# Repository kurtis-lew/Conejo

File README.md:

# Conejo

## Overview

The Conejo is an OSH split, columnar-staggered, 54-key keyboard inspired by the [Iris](https://keeb.io/products/iris-keyboard-split-ergonomic-keyboard), [Lily58](https://github.com/kata0510/Lily58), and [Corne](https://github.com/foostan/crkbd) and powered by the [ZMK Firmware](https://github.com/zmkfirmware/zmk).

For more information, see the [project wiki](https://github.com/kurtis-lew/Conejo/wiki).

## Repository Structure
- KiCAD Project files are located in the root folder
- Gerbers for PCB fabrication are located in `exports/gerbers`.
- `.3mf` files for 3D printing cases are located in `exports/3D`
- An interactive BOM is located in `exports/bom`

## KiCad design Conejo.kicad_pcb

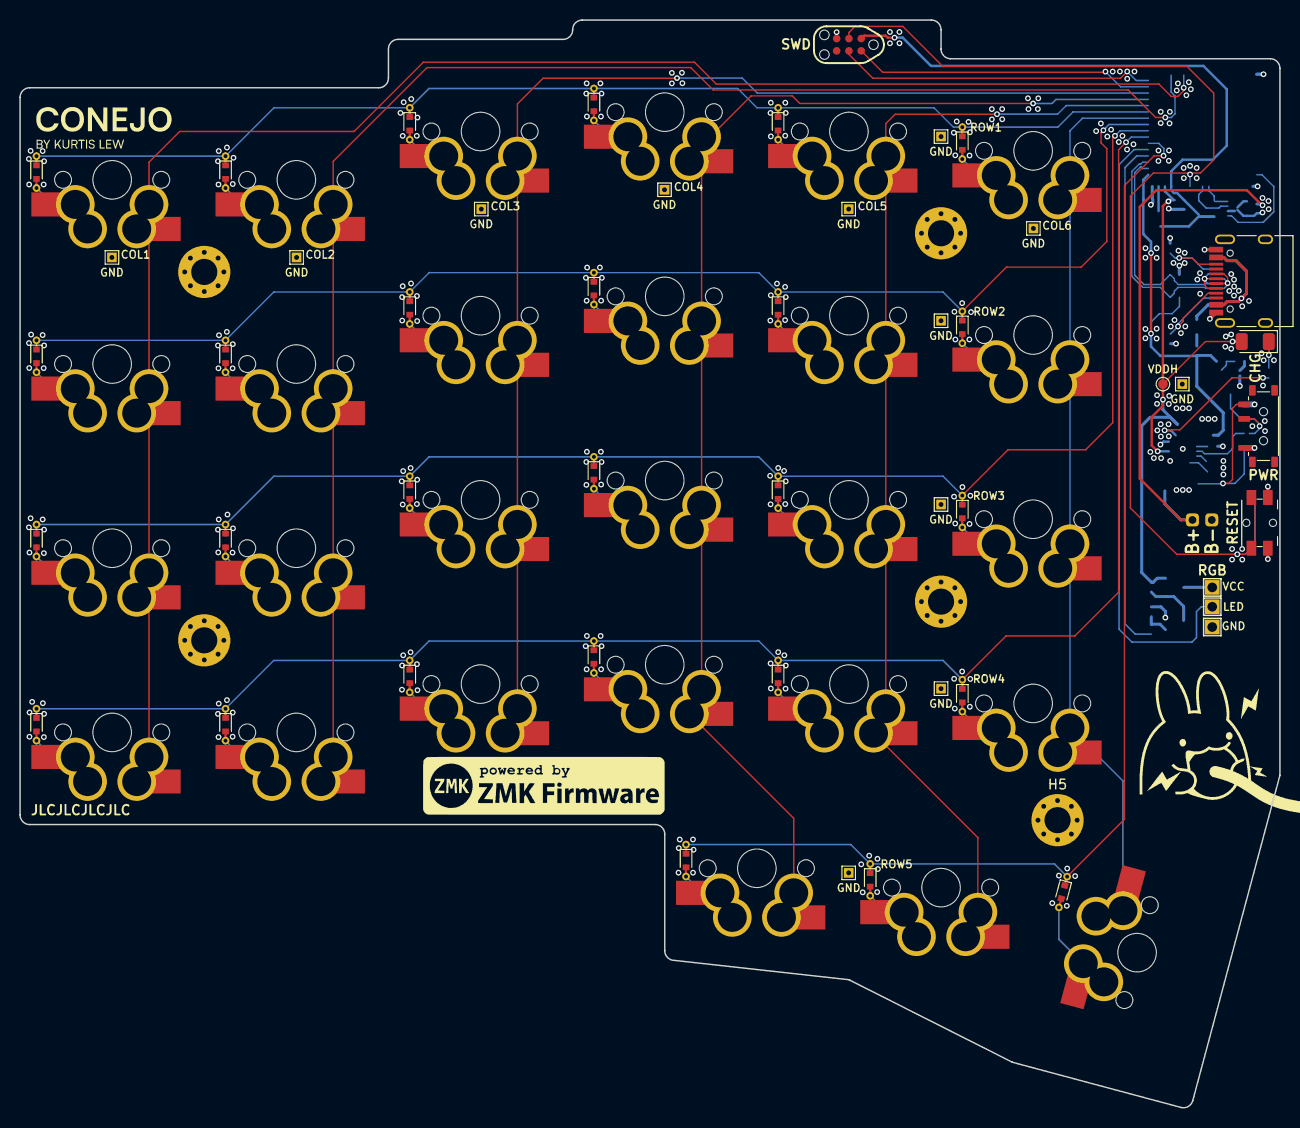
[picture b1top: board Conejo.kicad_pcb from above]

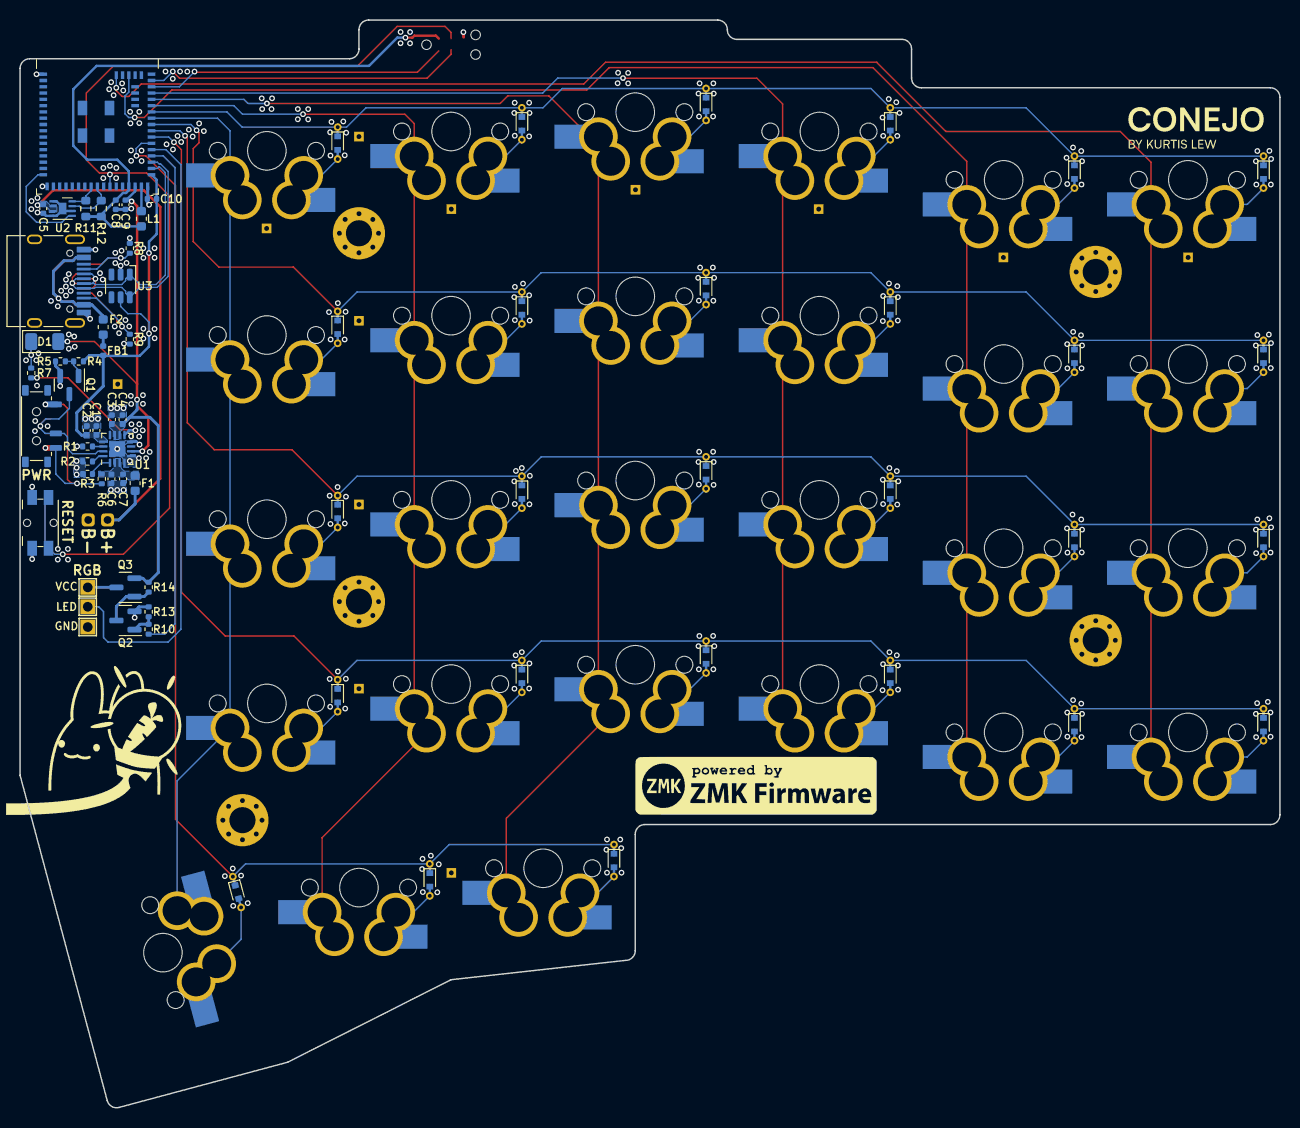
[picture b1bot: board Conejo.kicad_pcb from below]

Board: 4 copper layers, 130.3 x 112.5 mm, 116 parts (40 on the bottom side), 70 nets.

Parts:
C1, C2, C3, C4, C6, C7, C8, C9, C10: 4u7F; C_0402_1005Metric
C5: 100nF; C_0402_1005Metric
D1: CHG; LED_1206_3216Metric (Reversible)
D3, D4, D5, D6, D7, D8, D9, D10, D11, D12, D13, D14, D15, D16, D17, D18, D19, D20, D21, D22, D23, D24, D25, D26, D27, D28, D29: 1N4148; D_SOD-523 (Reversible)
F1, F2: 500mA; Fuse_0603_1608Metric
FB1: 120R@100MHz; L_0402_1005Metric
G1, G2: LOGO; Powered_By_ZMK (Large)
H1, H2, H3, H4, H5: M2.5; MountingHole_2.7mm_Pad_Via
J1: BATT; Battery Header
J2: HRO_TYPE-C-31-M-12; USB_C_Receptacle_HRO_TYPE-C-31-M-12 (Reversible)
J3: JTAG_TC2030; CON_TC2030_outlined
J4: RGB; LED Header
L1: 10uH; L_0603_1608Metric
Q1, Q2: 2N7002; SOT-23
Q3: AO3407; SOT-23
R1: RTMR; R_0402_1005Metric
R2: RSET; R_0402_1005Metric
R3, R5, R13, R14: 10K; R_0402_1005Metric
R4, R10: 100R; R_0402_1005Metric
R6: 100K; R_0402_1005Metric
R7: 1K5; R_0402_1005Metric
R8, R9: 5K1; R_0402_1005Metric
R11, R12: 5K1; R_0603_1608Metric
SW1: PWR; SW_MSK12C02-HB (Reversible)
SW2, SW3, SW4, SW5, SW6, SW7, SW8, SW9, SW10, SW11, SW12, SW13, SW14, SW15, SW16, SW17, SW18, SW19, SW20, SW21, SW22, SW23, SW24, SW25, SW26, SW27: MX Hotswap; MXOnly-1U-Hotswap (Reversible)
SW28: MX Hotswap; MXOnly-1.5U-Hotswap (Reversible)
SW29: RESET; Panasonic_EVQPUL_EVQPUC (Reversible)
TP1, TP1#2, TP1#3, TP1#4, TP1#5, TP1#6, TP1#7, TP1#8, TP1#9, TP1#10, TP1#11, TP1#12: GND; TestPoint_THTPad_1.0x1.0mm_Drill0.5mm
TP2: VDDH; TestPoint_Pad_D1.0mm
U1: BQ24075RGT; VQFN-16-1EP_3x3mm_P0.5mm_EP1.6x1.6mm
U2: MAX17048; TDFN-8-1EP_2x2mm_P0.5mm_EP0.8x1.2mm
U3: SRV05-4; SOT-23-6-routable
U4: MS88SF3; MS88SF3_V2

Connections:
+5V: C1.1, C2.2, C10.1, FB1.2, R4.1, U1.13 (IN), U3.5 (VP), U4.35 (VBUS)
+BATT: C5.1, F1.2, J1.1, U2.2 (CELL), U2.3 (VDD)
/Power Management/CHG: R7.1, U1.9 (~CHG)
/Power Management/ISET: R2.2, U1.16 (ISET)
/Power Management/SYSOFF: Q1.3 (D), SW1.2 (B), U1.15 (SYSOFF)
/Power Management/TMR: R1.2, U1.14 (TMR)
/Power Management/TS: R3.2, U1.1 (TS)
/USB-C/CC1: J2.A5 (CC1), R9.1
/USB-C/CC2: J2.B5 (CC2), R8.2
ALERT: U2.5 (ALERT), U4.17 (P0.26)
COL1: SW2.1, SW3.1, SW4.1, SW5.1, U4.56 (P0.10)
COL2: SW6.1, SW7.1, SW8.1, SW9.1, U4.54 (P1.06)
COL3: SW10.1, SW11.1, SW12.1, SW13.1, U4.48 (P0.25)
COL4: SW14.1, SW15.1, SW16.1, SW17.1, SW18.1, U4.47 (P1.00)
COL5: SW19.1, SW20.1, SW21.1, SW22.1, SW23.1, U4.46 (P0.24)
COL6: SW24.1, SW25.1, SW26.1, SW27.1, SW28.1, U4.44 (P0.20)
D+: J2.A6 (D+), J2.B6 (D+), U3.6 (IO4), U4.37 (D+)
D-: J2.A7 (D-), J2.B7 (D-), U3.1 (IO1), U4.36 (D-)
DCCH: L1.1, U4.33 (DCCH)
EXT_PWR: J4.1, Q3.3 (D)
EXT_PWR_EN: R10.1, U4.38 (P0.19)
GND: C1.2, C2.1, C3.2, C4.2, C5.2, C6.2, C7.2, C8.2, C9.2, C10.2, H1.1, H2.1, H3.1, H4.1, H5.1, J1.2, J2.A1 (GND), J2.A12 (GND), J2.B1 (GND), J2.B12 (GND), J2.S1 (SHIELD), J3.5 (GND), J4.3, Q1.2 (S), Q2.2 (S), R1.1, R2.1, R3.1, R5.1, R8.1, R9.2, R13.1, SW1.1 (A), SW29.1, TP1.1, TP1#2.1, TP1#3.1, TP1#4.1, TP1#5.1, TP1#6.1, TP1#7.1, TP1#8.1, TP1#9.1, TP1#10.1, TP1#11.1, TP1#12.1, U1.4 (~CE), U1.5 (EN2), U1.8 (VSS), U1.17 (VSS), U2.1 (CTG), U2.4 (GND), U2.6 (QSTRT), U2.9 (GND), U3.2 (VN), U4.1 (GND), U4.18 (GND), U4.34 (GND)
LED_MOSI: J4.2, U4.39 (P0.13)
unnamed: D1.1 (K), R7.2
unnamed: D3.2 (A), SW2.2
unnamed: D4.2 (A), SW3.2
unnamed: D5.2 (A), SW4.2
unnamed: D6.2 (A), SW5.2
unnamed: D7.2 (A), SW6.2
unnamed: D8.2 (A), SW7.2
unnamed: D9.2 (A), SW8.2
unnamed: D10.2 (A), SW9.2
unnamed: D11.2 (A), SW10.2
unnamed: D12.2 (A), SW11.2
unnamed: D13.2 (A), SW12.2
unnamed: D14.2 (A), SW13.2
unnamed: D15.2 (A), SW14.2
unnamed: D16.2 (A), SW15.2
unnamed: D17.2 (A), SW16.2
unnamed: D18.2 (A), SW17.2
unnamed: D19.2 (A), SW18.2
unnamed: D20.2 (A), SW19.2
unnamed: D21.2 (A), SW20.2
unnamed: D22.2 (A), SW21.2
unnamed: D23.2 (A), SW22.2
unnamed: D24.2 (A), SW23.2
unnamed: D25.2 (A), SW24.2
unnamed: D26.2 (A), SW25.2
unnamed: D27.2 (A), SW26.2
unnamed: D28.2 (A), SW27.2
unnamed: D29.2 (A), SW28.2
unnamed: F2.2, FB1.1
unnamed: Q1.1 (G), R4.2, R5.2
unnamed: Q2.1 (G), R10.2, R13.2
unnamed: Q2.3 (D), Q3.1 (G), R14.1
unnamed: R6.1, SW1.3 (C)
RESET: J3.3 (~RST), SW29.2, U4.28 (P0.18/RST)
ROW1: D3.1 (K), D7.1 (K), D11.1 (K), D15.1 (K), D20.1 (K), D25.1 (K), U4.45 (P0.22)
ROW2: D4.1 (K), D8.1 (K), D12.1 (K), D16.1 (K), D21.1 (K), D26.1 (K), U4.43 (P0.23)
ROW3: D5.1 (K), D9.1 (K), D13.1 (K), D17.1 (K), D22.1 (K), D27.1 (K), U4.42 (P0.21)
ROW4: D6.1 (K), D10.1 (K), D14.1 (K), D18.1 (K), D23.1 (K), D28.1 (K), U4.41 (P0.17)
ROW5: D19.1 (K), D24.1 (K), D29.1 (K), U4.40 (P0.15)
SCL: R12.1, U2.7 (SCL), U4.26 (P1.09)
SDA: R11.1, U2.8 (SDA), U4.25 (P0.08)
SWCLK: J3.4 (SWCLK), U4.50 (SWCLK)
SWDIO: J3.2 (SWDIO), U4.49 (SWDIO)
VBAT: C6.1, C7.1, F1.1, R6.2, U1.2 (BAT), U1.3 (BAT)
VBUS: F2.1, J2.A4 (VBUS), J2.A9 (VBUS), J2.B4 (VBUS), J2.B9 (VBUS)
VDD: C8.1, J3.1 (VCC), L1.2, R11.2, R12.2, U4.31 (VDD)
VDDH: C3.1, C4.1, C9.1, D1.2 (A), Q3.2 (S), R14.2, TP2.1, U1.6 (EN1), U1.10 (OUT), U1.11 (OUT), U4.32 (VDDH)

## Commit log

2022-07-09 feat(pcb): Version 0.1
2022-07-09 fix(pcb): Move thumb cluster in by 3mm
2022-07-09 fix(pcb): Move USB-C 1.5mm closer to the edge
2022-07-09 feat(pcb): Version 0.2
2022-07-09 feat(pcb): Version 0.2.1
2022-07-09 fix(schematic): Adjust charging parameters
2022-07-09 fix(pcb): Update column stagger measurement table
2022-07-09 fix(3D): Re-export 3D model for case design
2022-07-09 fix(schematic): Fix links to footprints
2022-07-10 fix(pcb): Add fillet to thumb cluster edge cut
2022-07-10 fix(schematic): Delete Moko_MK08A.kicad_sch
2022-07-10 refactor!!!(repository): Rename from Athena54 to Conejo
2022-07-10 fix(docs): Update header to reflect renaming
2022-07-10 fix(schematic): Further updates to referencing footprints and symbols
2022-07-10 fix(repo): Update .gitignore
2022-07-10 refactor(pcb): Update paths to 3D models, whole board .STEP
    Delete EVQPU-LC-02K.STEP
2022-07-11 feat(pcb): Version 0.2.2
    - Update MS88SF3 footprint
    - Create thumb cluster silksscreen
    - Separate NTPH and PTH drill files
2022-07-12 fix(pcb): Finalize part selection
2022-07-13 fix(schematic): Fix inductor value in DCCH LC filter
2022-07-13 feat(pcb): Version 0.2.3
    - Switched vertical traces on matrix to back copper
    - Added GND vias for all diodes
2022-07-15 feat(pcb): Version 0.3
    - Move components entirely to back copper :tada:
    - Update silkscreen legibility to enhance ease of component placement
    - Fix I2C pullup resistors
    - Replace incorrect value of 1K5 with 5K1
    - Update footprint to 0603_1608 to fit VDD traces underneath, compared to original 0402_1005 footprint
    - Increase text width on RESET button, POWER Switch, and CHG LED
2022-07-15 fix(pcb): Update RGB header component placement
2022-07-16 feat(pcb): Version 0.3.1
2022-07-17 feat(pcb): Version 0.3.2
    - Move TC2030 footprint to accessible location
    - Move diodes to be outside of 14mmx14mm switch area
    - Update BOM to remove footprints that don't require placement
2022-07-17 fix(pcb): Update Gerbers with JLCPCB order number location
2022-07-17 feat(schematic): Add titles and individual sheet comments
2022-07-21 feat(pcb): Version 0.4
    - Prepare to move from JLC7628 stackup to JLC3313 stackup (Lowers dielectric constant from 4.6 to 4.05)
    - Increase mounting hole diameter back to 5.4mm
    - 6mil signals, 10mil power, 13 mil vias
    - 3W spacing wherever possible
2022-07-21 fix(pcb): Re-check GND vias around diodes
2022-07-22 feat(pcb): Version 0.4.1
    - Add oscilloscope probing pads/labels
2022-07-30 feat(pcb): Switch from 4.3mm NPTH mounting holes to M2 PTH
2022-08-01 feat(3D): Re-export model with M2 holes
2022-08-03 feat(3D): Re-export model with M3 holes with vias
2022-08-07 feat(pcb): Version 0.4.2
    - Add nameplate
    - Increase mounting hole size to M2.5
2022-08-08 feat(pcb): Update ConejoPlug.kicad_mod
    - Give the bunny elbows!
2022-08-20 feat(pcb): Version 1.0.0
    - Change decoupling capacitors from 4.7uF/1uF pairs to both 4.7uF
2022-08-21 fix(pcb/bom): Remove test points from BOM
2022-08-23 feat(3D): Update model for production release
2022-09-04 feat(3D): Export case models
2022-09-04 feat(repo): Add LICENSE
2022-09-04 feat(docs): Update README
2022-09-05 feat(3D): Export bottom covers
2022-10-11 feat(docs): Upload Interim Product Image
